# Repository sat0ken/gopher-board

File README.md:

# gopher-board

Kicad Project for fun tinygo!

## Licence

The Go gopher was designed by Renee French.
[http://reneefrench.blogspot.com/](http://reneefrench.blogspot.com/)

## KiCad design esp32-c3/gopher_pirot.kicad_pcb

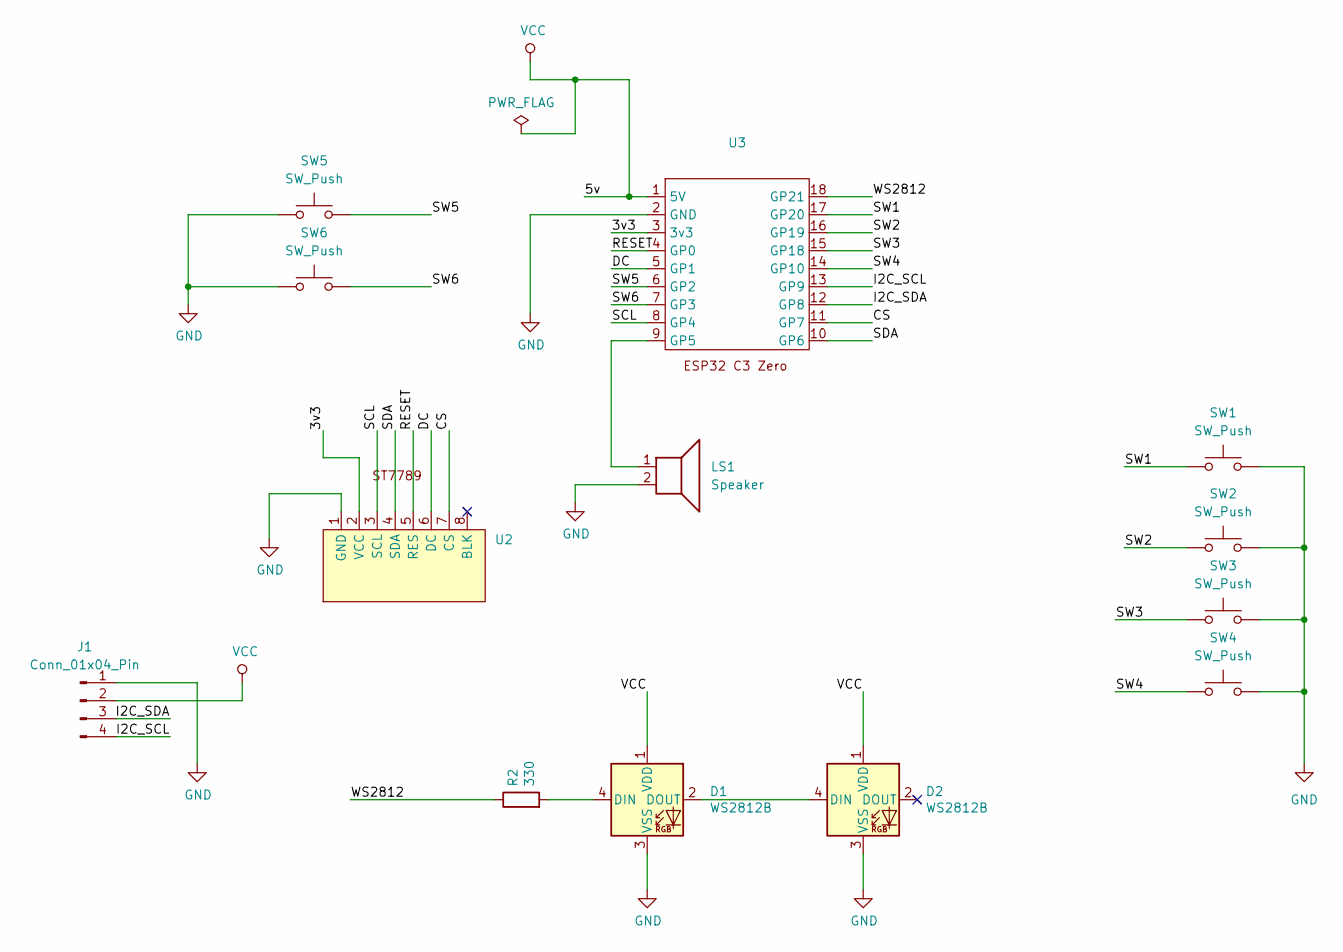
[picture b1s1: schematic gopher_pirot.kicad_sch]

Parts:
D1, D2: WS2812B; LED_WS2812B_PLCC4_5.0x5.0mm_P3.2mm
J1: Conn_01x04_Pin; PinHeader_1x04_P2.00mm_Vertical
LS1: Speaker; Buzzer_TDK_PS1240P02BT_D12.2mm_H6.5mm
R2: 330; R_0805_2012Metric
SW1, SW2, SW3, SW4, SW5, SW6: SW_Push; SW_PUSH_6mm_H4.3mm
U2: PinSocket_1x08_P2.54mm_Vertical
U3: my-esp32-c3-zero

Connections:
/3v3: U2.2 (VCC), U3.3 (3v3)
/CS: U2.7 (CS), U3.11 (GP7)
/DC: U2.6 (DC), U3.5 (GP1)
/I2C_SCL: J1.4, U3.13 (GP9)
/I2C_SDA: J1.3, U3.12 (GP8)
/RESET: U2.5 (RES), U3.4 (GP0)
/SCL: U2.3 (SCL), U3.8 (GP4)
/SDA: U2.4 (SDA), U3.10 (GP6)
/SW1: SW1.1, U3.17 (GP20)
/SW2: SW2.1, U3.16 (GP19)
/SW3: SW3.1, U3.15 (GP18)
/SW4: SW4.1, U3.14 (GP10)
/SW5: SW5.2, U3.6 (GP2)
/SW6: SW6.2, U3.7 (GP3)
/WS2812: R2.1, U3.18 (GP21)
GND: D1.3 (VSS), D2.3 (VSS), J1.1, LS1.2, SW1.2, SW2.2, SW3.2, SW4.2, SW5.1, SW6.1, U2.1 (GND), U3.2 (GND)
unnamed: D1.4 (DIN), R2.2
unnamed: D1.2 (DOUT), D2.4 (DIN)
unnamed: LS1.1, U3.9 (GP5)
VCC: D1.1 (VDD), D2.1 (VDD), J1.2, U3.1 (5V)

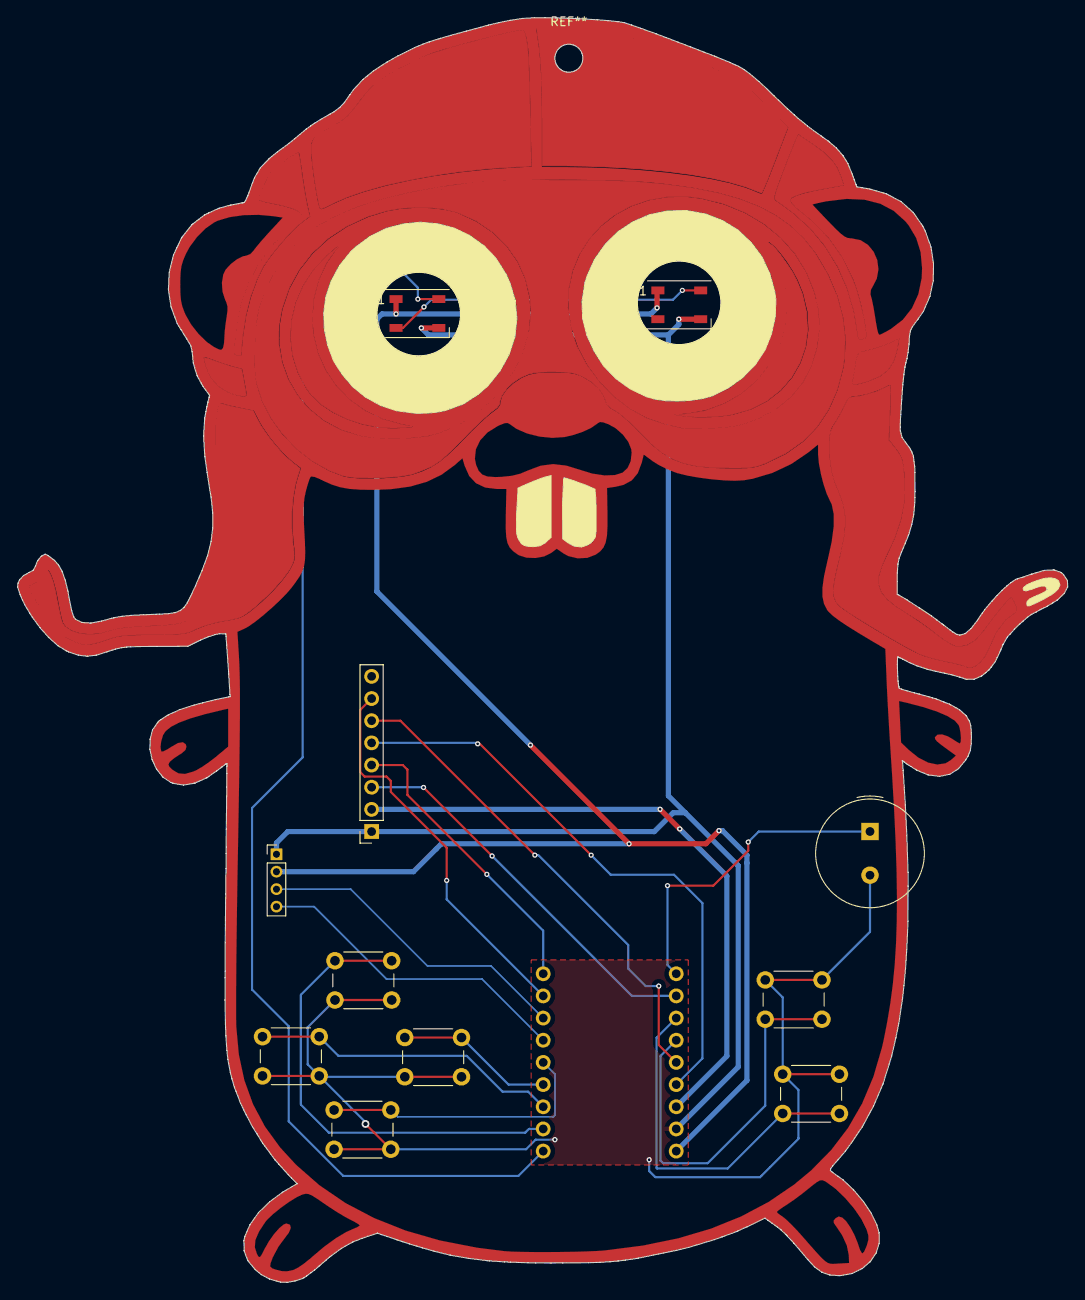
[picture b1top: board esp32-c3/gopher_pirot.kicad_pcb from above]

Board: 2 copper layers, 120.3 x 144.9 mm, 13 parts (1 on the bottom side), 20 nets.

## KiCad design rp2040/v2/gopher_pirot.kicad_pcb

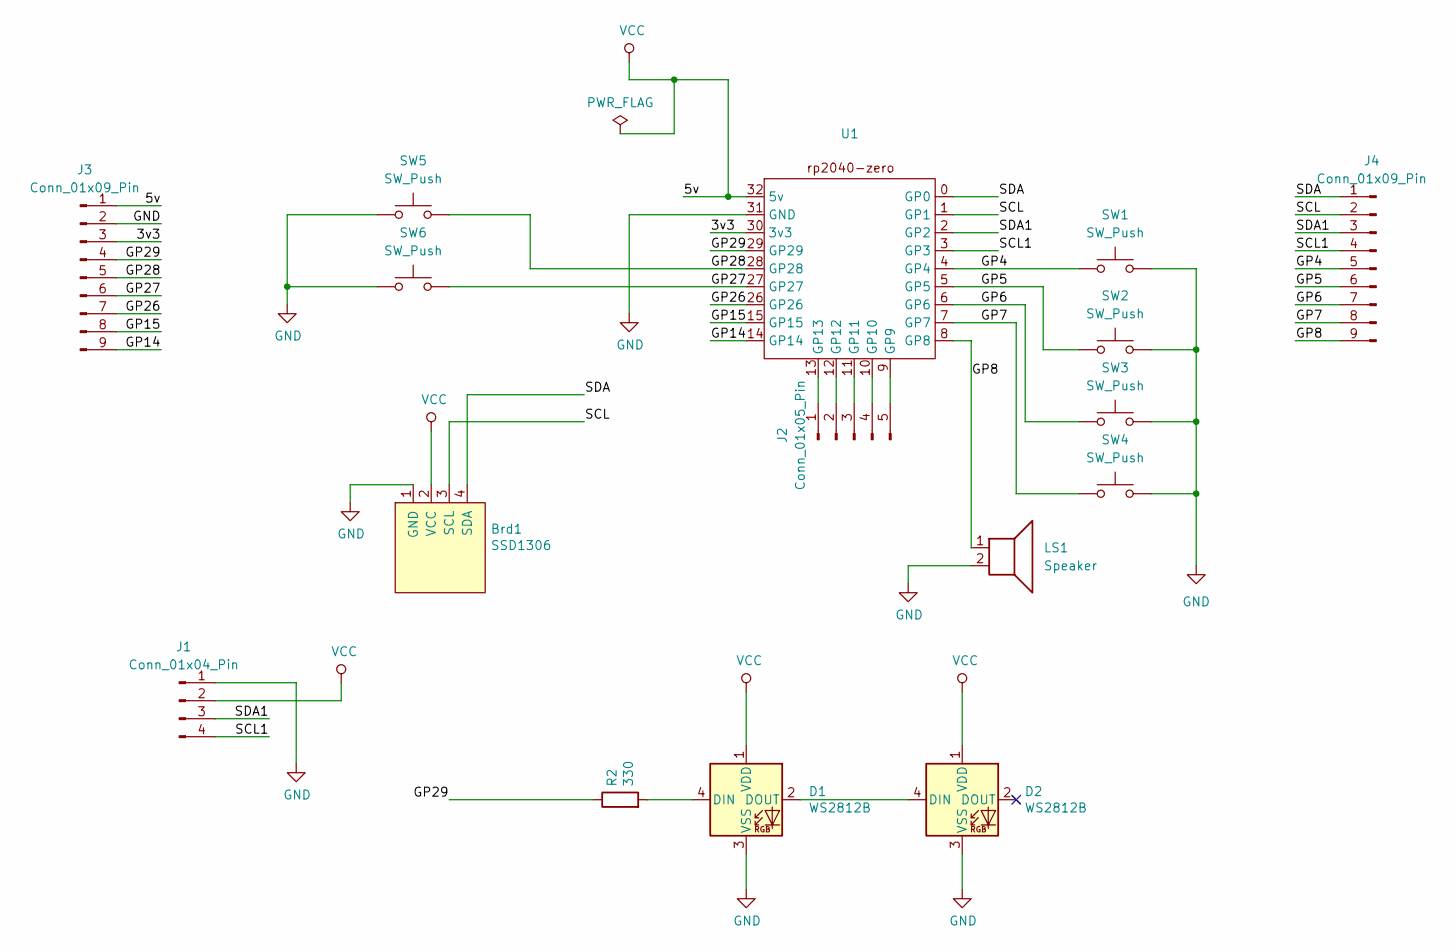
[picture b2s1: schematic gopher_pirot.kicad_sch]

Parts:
Brd1: SSD1306; PinSocket_1x04_P2.54mm_Vertical
D1, D2: WS2812B; LED_WS2812B_PLCC4_5.0x5.0mm_P3.2mm
J1: Conn_01x04_Pin; PinHeader_1x04_P2.00mm_Vertical
J2: Conn_01x05_Pin; PinSocket_1x05_P2.54mm_Vertical
J3, J4: Conn_01x09_Pin; PinSocket_1x09_P2.54mm_Vertical
LS1: Speaker; Buzzer_TDK_PS1240P02BT_D12.2mm_H6.5mm
R2: 330; R_0805_2012Metric
SW1, SW2, SW3, SW4, SW5, SW6: SW_Push; SW_PUSH_6mm_H4.3mm
U1: my-rp2040-zero

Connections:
/3v3: J3.3, U1.30 (3v3)
/GP4: J4.5, SW1.1, U1.4 (GP4)
/GP5: J4.6, SW2.1, U1.5 (GP5)
/GP6: J4.7, SW3.1, U1.6 (GP6)
/GP7: J4.8, SW4.1, U1.7 (GP7)
/GP8: J4.9, LS1.1, U1.8 (GP8)
/GP14: J3.9, U1.14 (GP14)
/GP15: J3.8, U1.15 (GP15)
/GP26: J3.7, U1.26 (GP26)
/GP27: J3.6, SW6.2, U1.27 (GP27)
/GP28: J3.5, SW5.2, U1.28 (GP28)
/GP29: J3.4, R2.1, U1.29 (GP29)
/SCL: Brd1.3 (SCL), J4.2, U1.1 (GP1)
/SCL1: J1.4, J4.4, U1.3 (GP3)
/SDA: Brd1.4 (SDA), J4.1, U1.0 (GP0)
/SDA1: J1.3, J4.3, U1.2 (GP2)
GND: Brd1.1 (GND), D1.3 (VSS), D2.3 (VSS), J1.1, J3.2, LS1.2, SW1.2, SW2.2, SW3.2, SW4.2, SW5.1, SW6.1, U1.31 (GND)
unnamed: D1.4 (DIN), R2.2
unnamed: D1.2 (DOUT), D2.4 (DIN)
unnamed: J2.1, U1.13 (GP13)
unnamed: J2.2, U1.12 (GP12)
unnamed: J2.3, U1.11 (GP11)
unnamed: J2.4, U1.10 (GP10)
unnamed: J2.5, U1.9 (GP9)
VCC: Brd1.2 (VCC), D1.1 (VDD), D2.1 (VDD), J1.2, J3.1, U1.32 (5v)

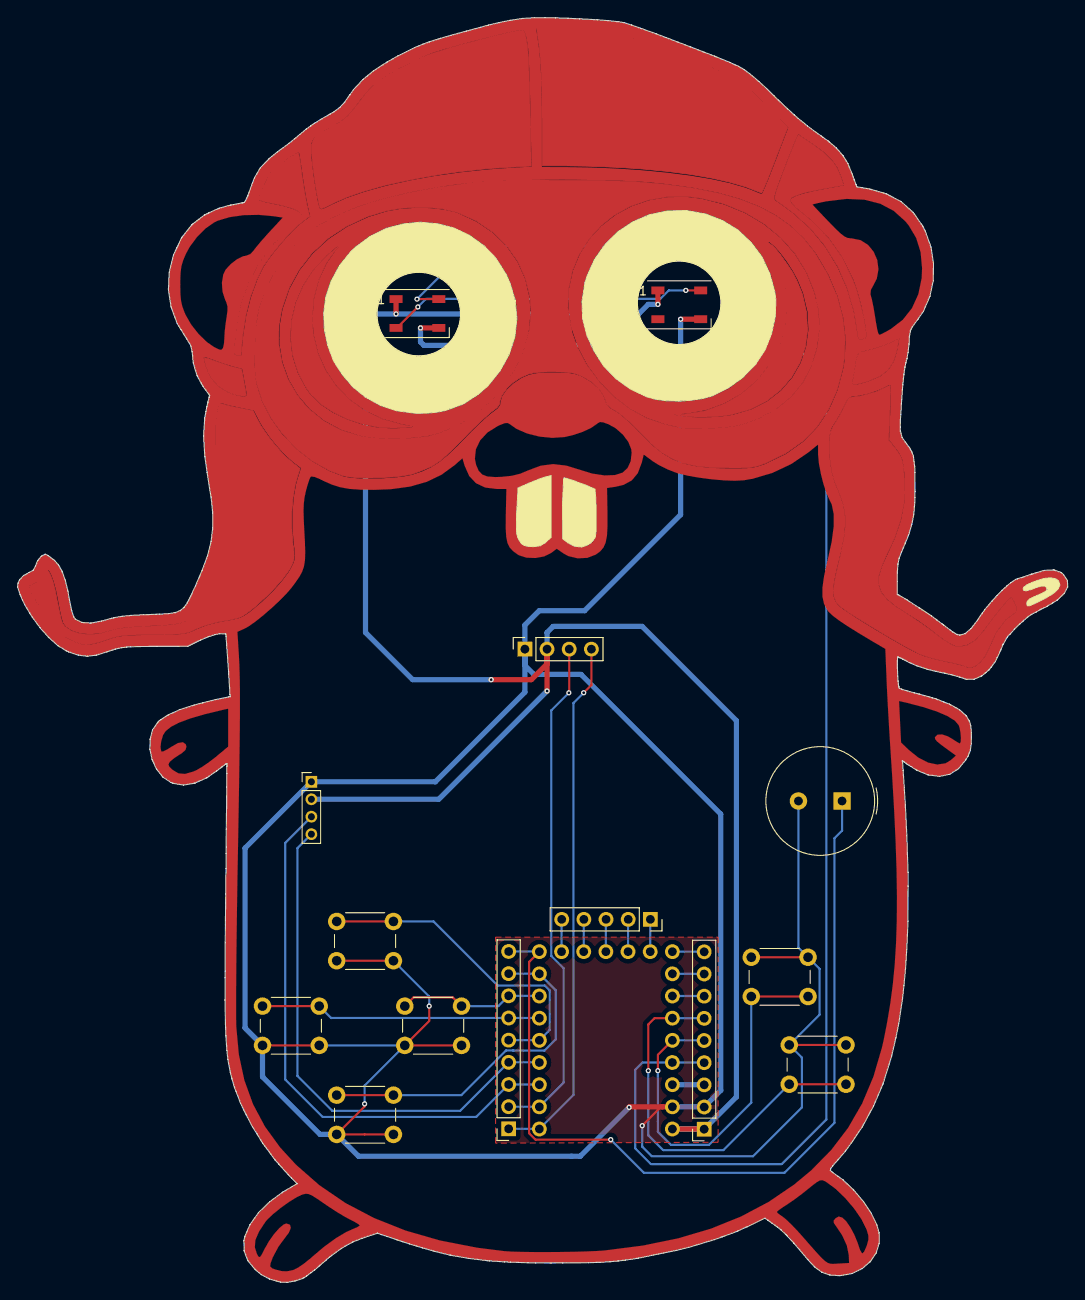
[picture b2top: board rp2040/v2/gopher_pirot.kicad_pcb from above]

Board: 2 copper layers, 120.3 x 144.9 mm, 16 parts (1 on the bottom side), 25 nets.

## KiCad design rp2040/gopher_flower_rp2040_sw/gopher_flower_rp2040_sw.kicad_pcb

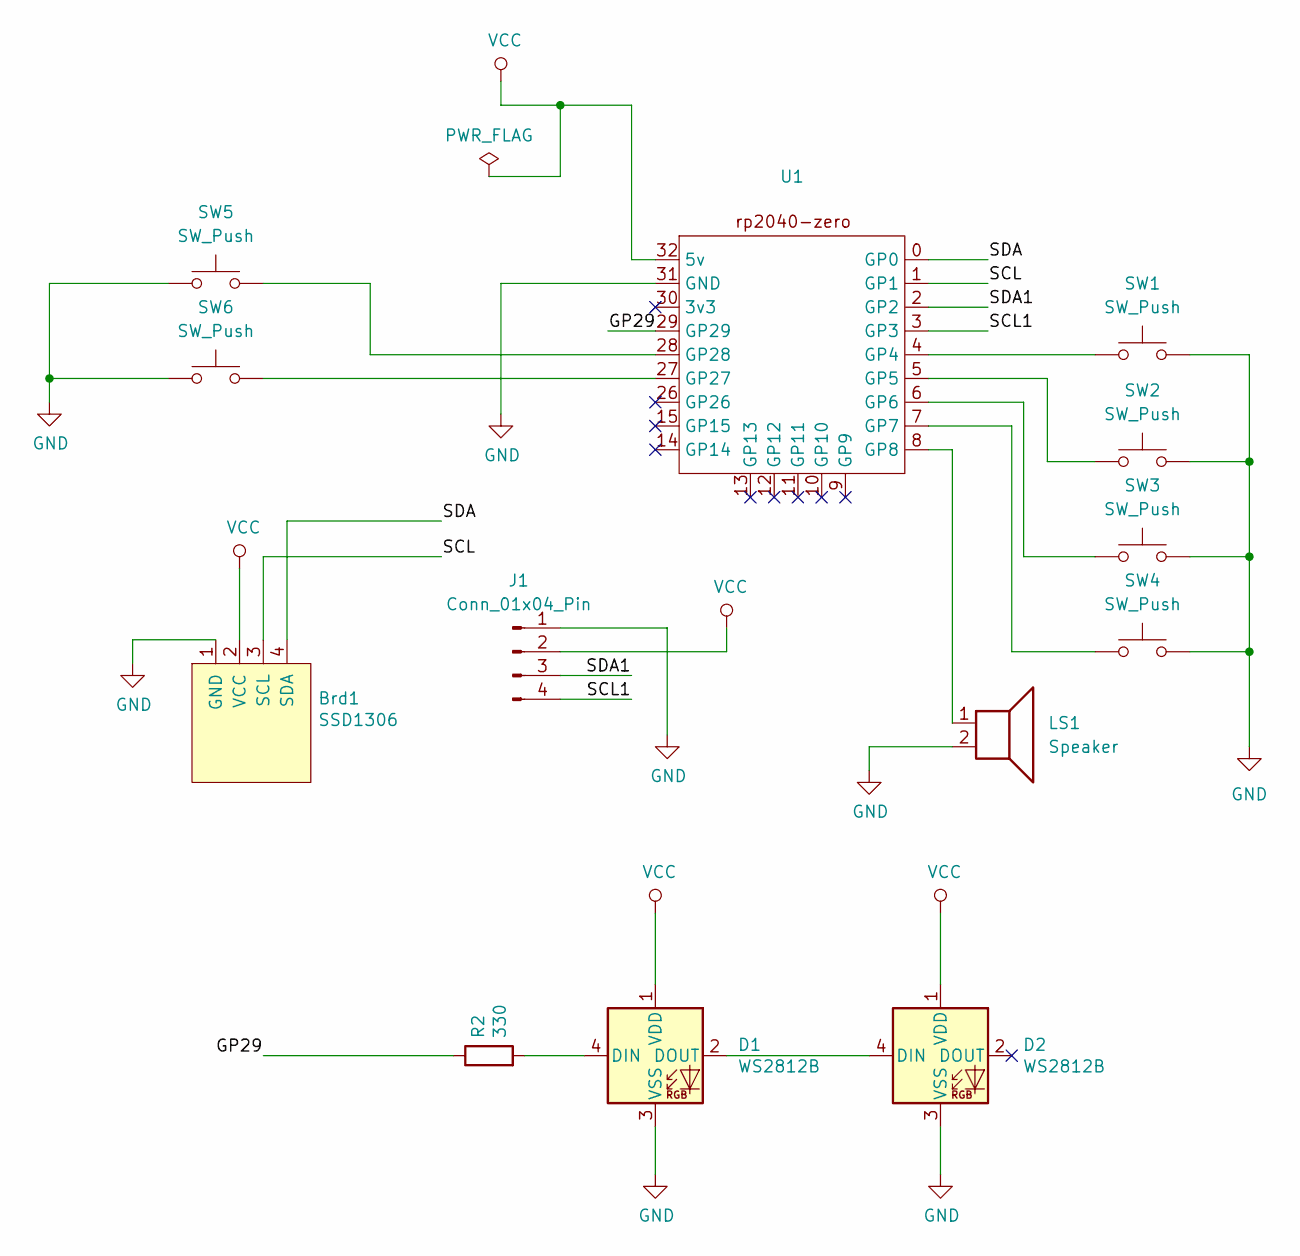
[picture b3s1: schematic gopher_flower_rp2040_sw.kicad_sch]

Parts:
Brd1: SSD1306; 128x64OLED
D1, D2: WS2812B; LED_WS2812B_PLCC4_5.0x5.0mm_P3.2mm
J1: Conn_01x04_Pin; PinHeader_1x04_P2.00mm_Vertical
LS1: Speaker; Buzzer_TDK_PS1240P02BT_D12.2mm_H6.5mm
R2: 330; R_0805_2012Metric
SW1, SW2, SW3, SW4, SW5, SW6: SW_Push; SW_PUSH_6mm_H4.3mm
U1: my-rp2040-zero

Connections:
/GP29: R2.1, U1.29 (GP29)
/SCL: Brd1.3 (SCL), U1.1 (GP1)
/SCL1: J1.4, U1.3 (GP3)
/SDA: Brd1.4 (SDA), U1.0 (GP0)
/SDA1: J1.3, U1.2 (GP2)
GND: Brd1.1 (GND), D1.3 (VSS), D2.3 (VSS), J1.1, LS1.2, SW1.2, SW2.2, SW3.2, SW4.2, SW5.1, SW6.1, U1.31 (GND)
unnamed: D1.4 (DIN), R2.2
unnamed: D1.2 (DOUT), D2.4 (DIN)
unnamed: SW1.1, U1.4 (GP4)
unnamed: SW2.1, U1.5 (GP5)
unnamed: SW3.1, U1.6 (GP6)
unnamed: SW4.1, U1.7 (GP7)
unnamed: LS1.1, U1.8 (GP8)
unnamed: SW6.2, U1.27 (GP27)
unnamed: SW5.2, U1.28 (GP28)
VCC: Brd1.2 (VCC), D1.1 (VDD), D2.1 (VDD), J1.2, U1.32 (5v)

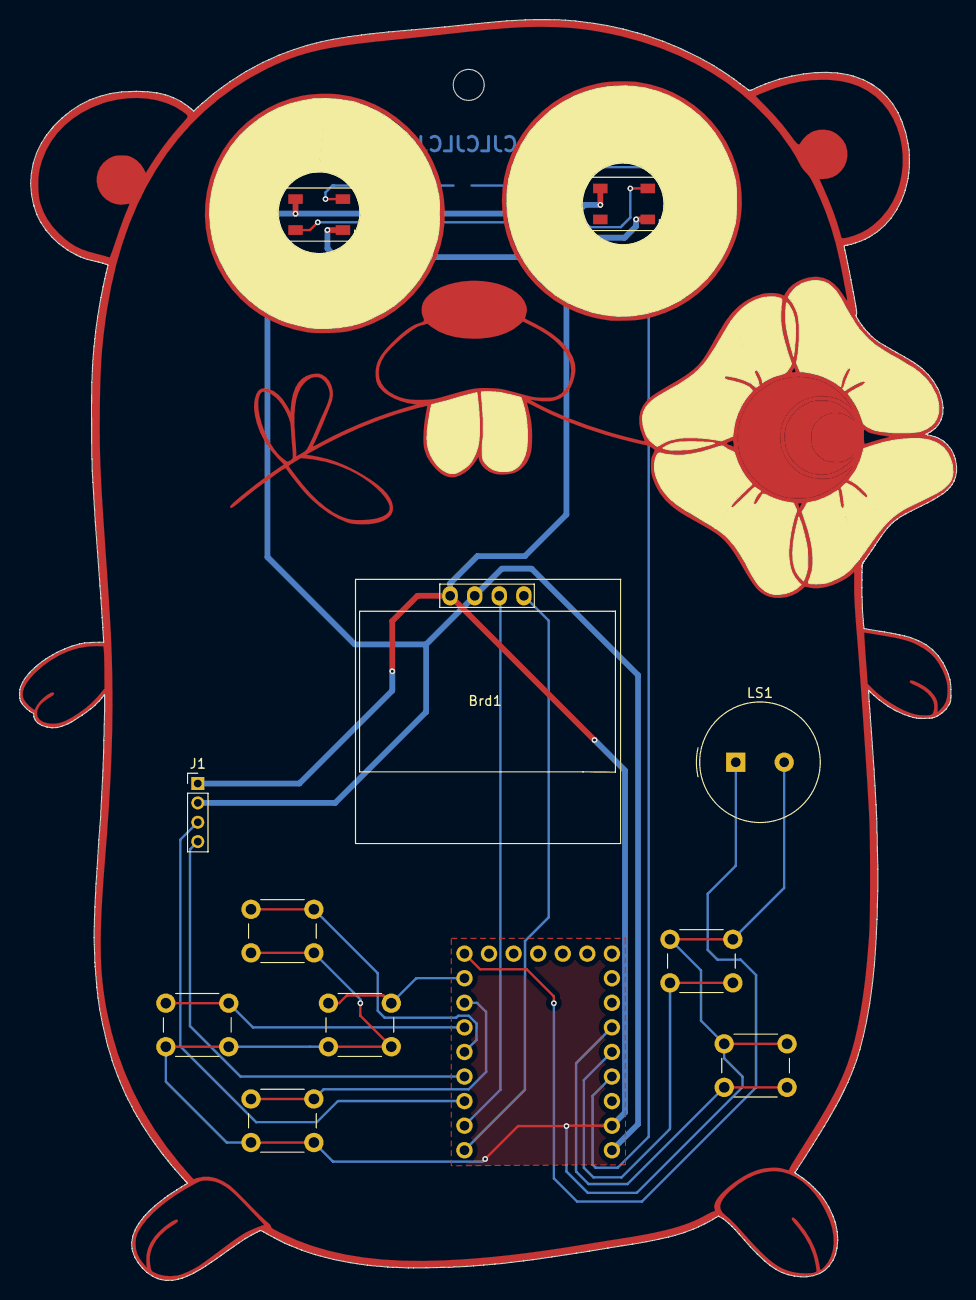
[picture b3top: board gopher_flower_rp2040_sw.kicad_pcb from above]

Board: 2 copper layers, 96.8 x 130.3 mm, 13 parts (1 on the bottom side), 16 nets.

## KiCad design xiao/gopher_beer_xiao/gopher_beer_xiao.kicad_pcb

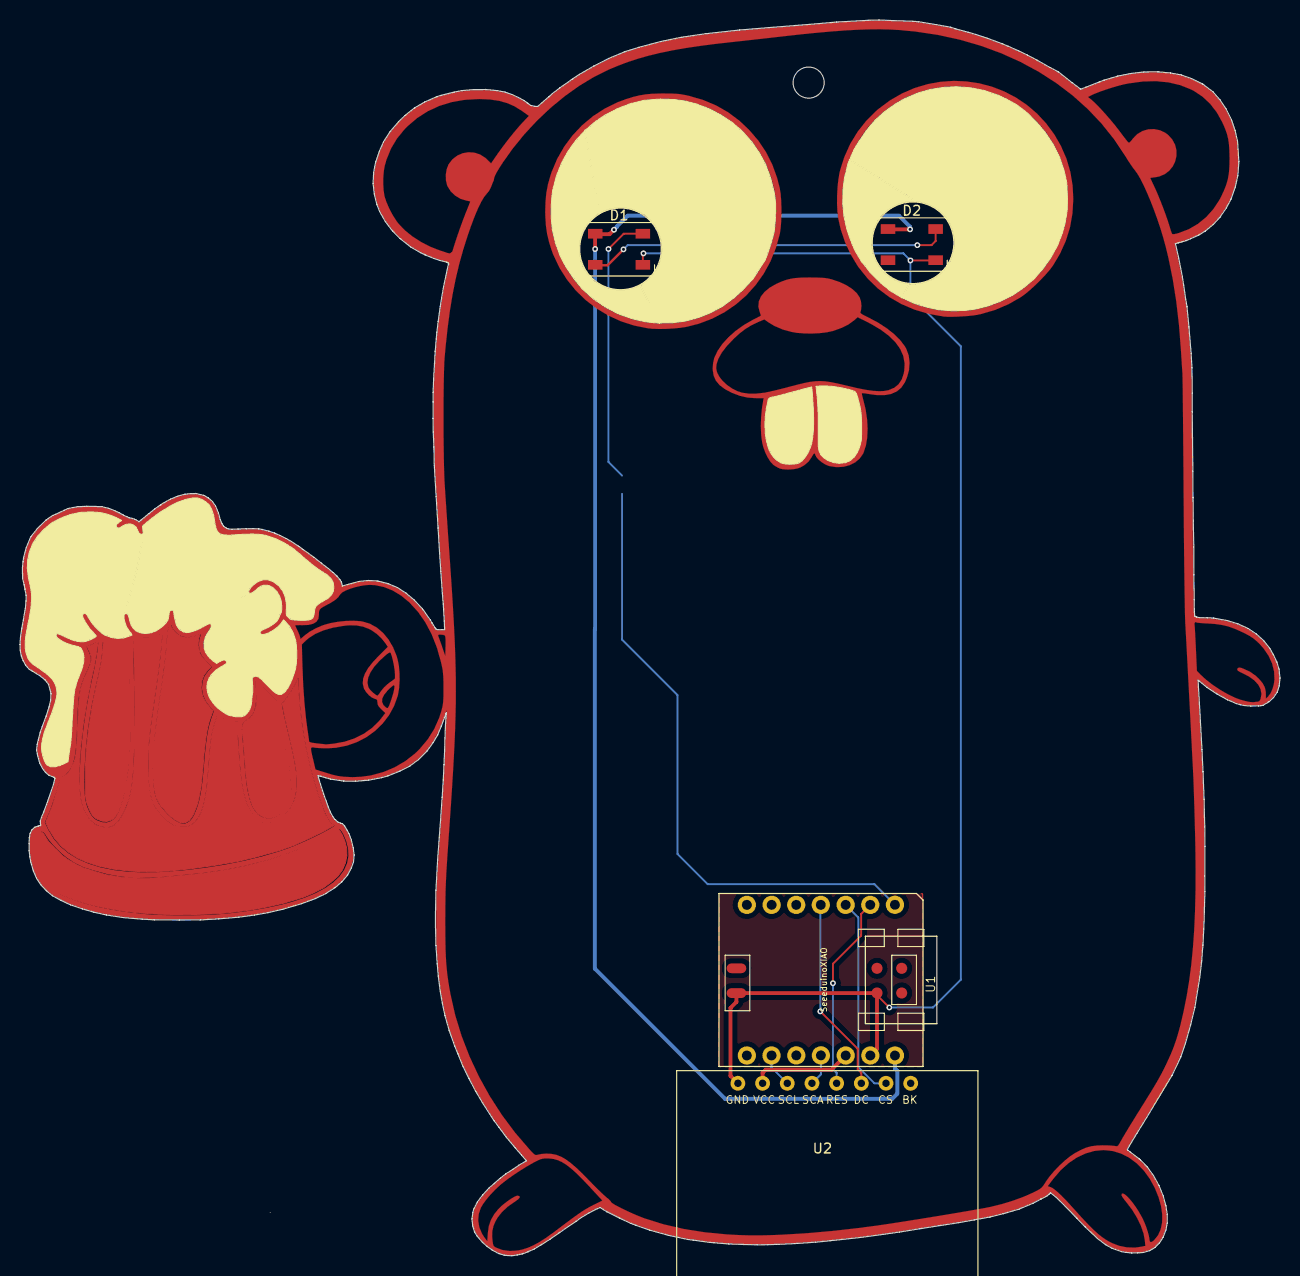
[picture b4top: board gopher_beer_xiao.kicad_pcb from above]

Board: 2 copper layers, 129.6 x 127.2 mm, 5 parts (1 on the bottom side), 11 nets.

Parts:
D1, D2: WS2812B; LED_WS2812B_PLCC4_5.0x5.0mm_P3.2mm
R2: 330; R_0805_2012Metric
U1: SeeeduinoXIAO; Seeeduino XIAO-MOUDLE14P-2.54-21X17.8MM_PinSocket
U2: ST7789_240x240; st7789_135x240

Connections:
/3v3: U1.12, U2.2
/CS: U1.3, U2.7
/DC: U1.4, U2.6
/PA02: R2.1, U1.1
/RES: U1.2, U2.5
/SCK: U1.9, U2.3
/SDA: U1.11, U2.4
GND: D1.3, D2.3, U1.13, U1.16, U1.20, U2.1
unnamed: D1.2, D2.4
unnamed: D1.4, R2.2
VCC: D1.1, D2.1, U1.14, U1.15

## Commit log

2024-09-22 add files
2024-09-22 add proj
2024-10-14 rename
2026-06-06 add esp32 board
